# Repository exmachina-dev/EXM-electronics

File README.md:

```
____ _  _ _  _    ____ _    ____ ____ ___ ____ ____ _  _ _ ____ ____ 
|___  \/  |\/| __ |___ |    |___ |     |  |__/ |  | |\ | | |    [__  
|___ _/\_ |  |    |___ |___ |___ |___  |  |  \ |__| | \| | |___ ___] 
                                                                      
```

# EXM electronics

This repo contains all necessary files to design and produce PCBs for the ExMachina product range.

## File format and folder structure

Documentation files should be in PDF. Board image files can be in PNG or PDF.

PCB design files are in EAGLE Standard edition (7.4) file format.

The following are general rules to help maintain a consistent folder structure:

* All libraries are placed inside the shared libraries repository. It can be found
  on [Github](https://github.com/exmchina-dev/eagle-resources)

* One board for each project folder.  

* Mutiples revisions can be placed inside a subfolder. i.e. `SwitchEthernet/Rev A1`

* BOMs, partlists, spreadsheet and Gerber should placed inside a `MDP/` folder.  

## STATUS
|		Board		|	Rev  |		|
|-------------------|--------|------|
|DMX Proto			| Rev A1 | :ok: |
|Emergency Stop 	| Rev A3 | :ok: |
|EXM Encoder 		| Rev A1 | :ok: |
|EXM HMI LED 		| Rev A1 | :ok: |
|EXM Relay Four		| Rev A1 | :ok: |
|EXM Relay One		| Rev A3 | :ok: |
|EXM Relay Three	| Rev A2 | :ok: |
|Switch Ethernet 	| Rev A5 | :ok: |

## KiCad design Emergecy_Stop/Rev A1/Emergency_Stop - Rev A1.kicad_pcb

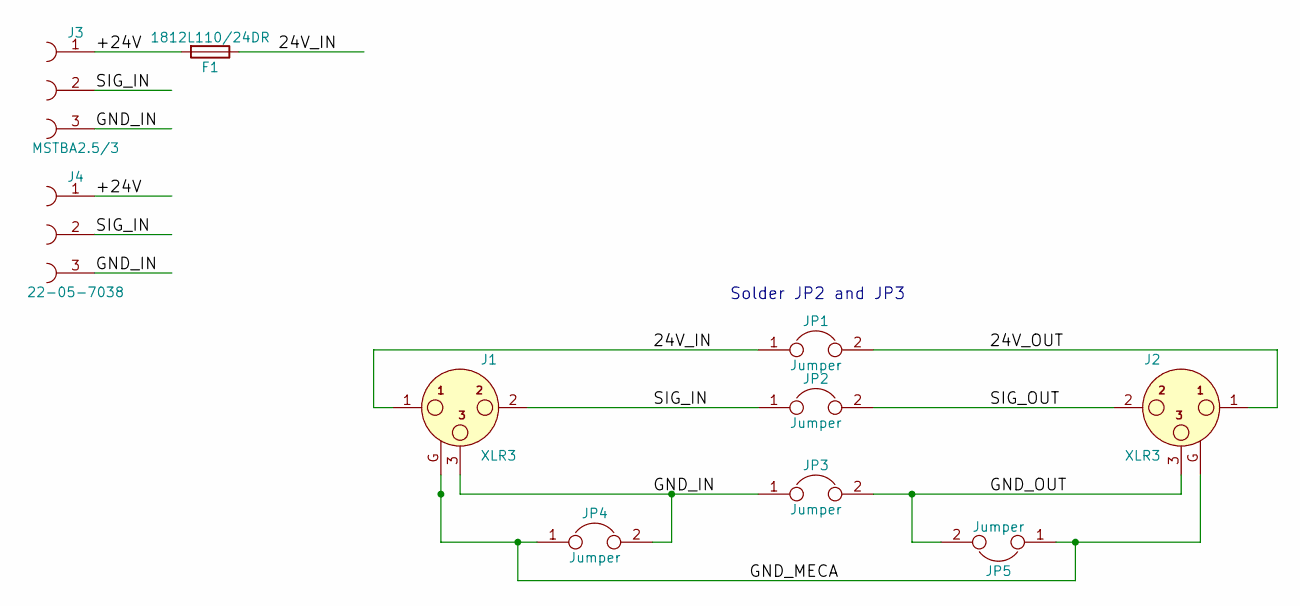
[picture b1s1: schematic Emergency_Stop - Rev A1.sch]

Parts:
F1: 1812L110/24DR; LittleFuse_1812L
J1: XLR3; NC3FAV2
J2: XLR3; NC3MAV
J3: MSTBA2.5/3; MSTBA3
J4: 22-05-7038
JP1, JP2, JP3, JP4, JP5: Jumper; GS2

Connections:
/24V_IN: F1.1, J1.1, JP1.1
/24V_OUT: J2.1, JP1.2
/+24V: F1.2, J3.1, J4.1
/GND_IN: J1.3, J3.3, J4.3, JP3.1, JP4.2
/GND_MECA: J1.G (GROUND), J2.G (GROUND), JP4.1, JP5.1
/GND_OUT: J2.3, JP3.2, JP5.2
/SIG_IN: J1.2, J3.2, J4.2, JP2.1
/SIG_OUT: J2.2, JP2.2

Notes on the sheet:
Solder JP2 and JP3

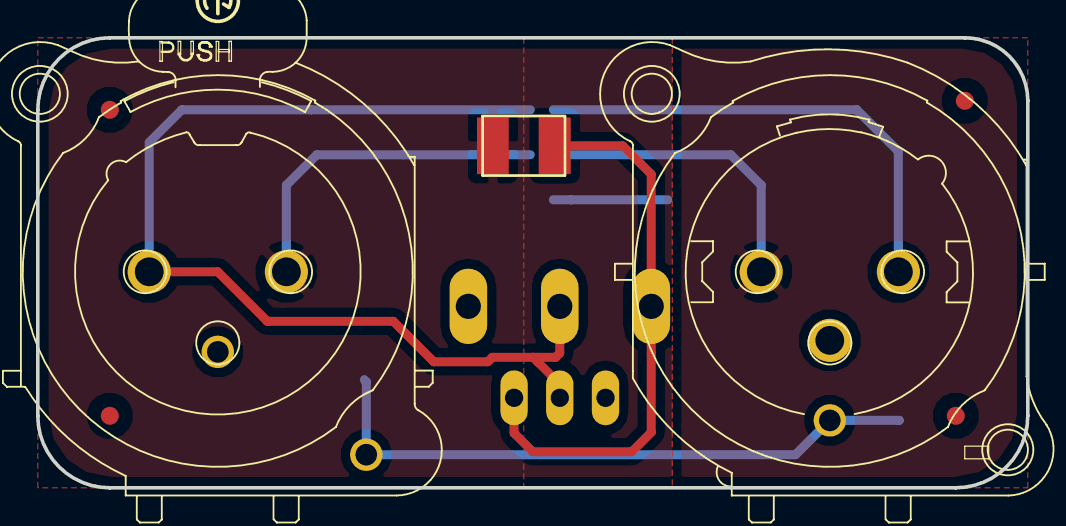
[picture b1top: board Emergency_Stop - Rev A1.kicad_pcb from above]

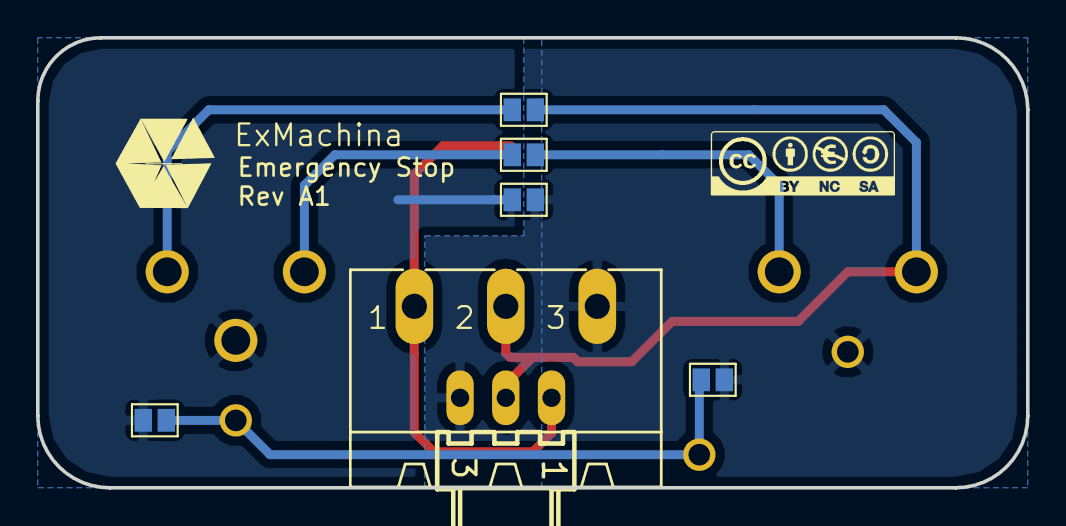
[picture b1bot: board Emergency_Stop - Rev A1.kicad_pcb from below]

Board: 2 copper layers, 55.0 x 25.0 mm, 12 parts (9 on the bottom side), 8 nets.

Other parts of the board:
S?: CC-BY-NC-SA
T3: EXMACHINA-LOGO-NAME; EXM-LOGO-BASELINE

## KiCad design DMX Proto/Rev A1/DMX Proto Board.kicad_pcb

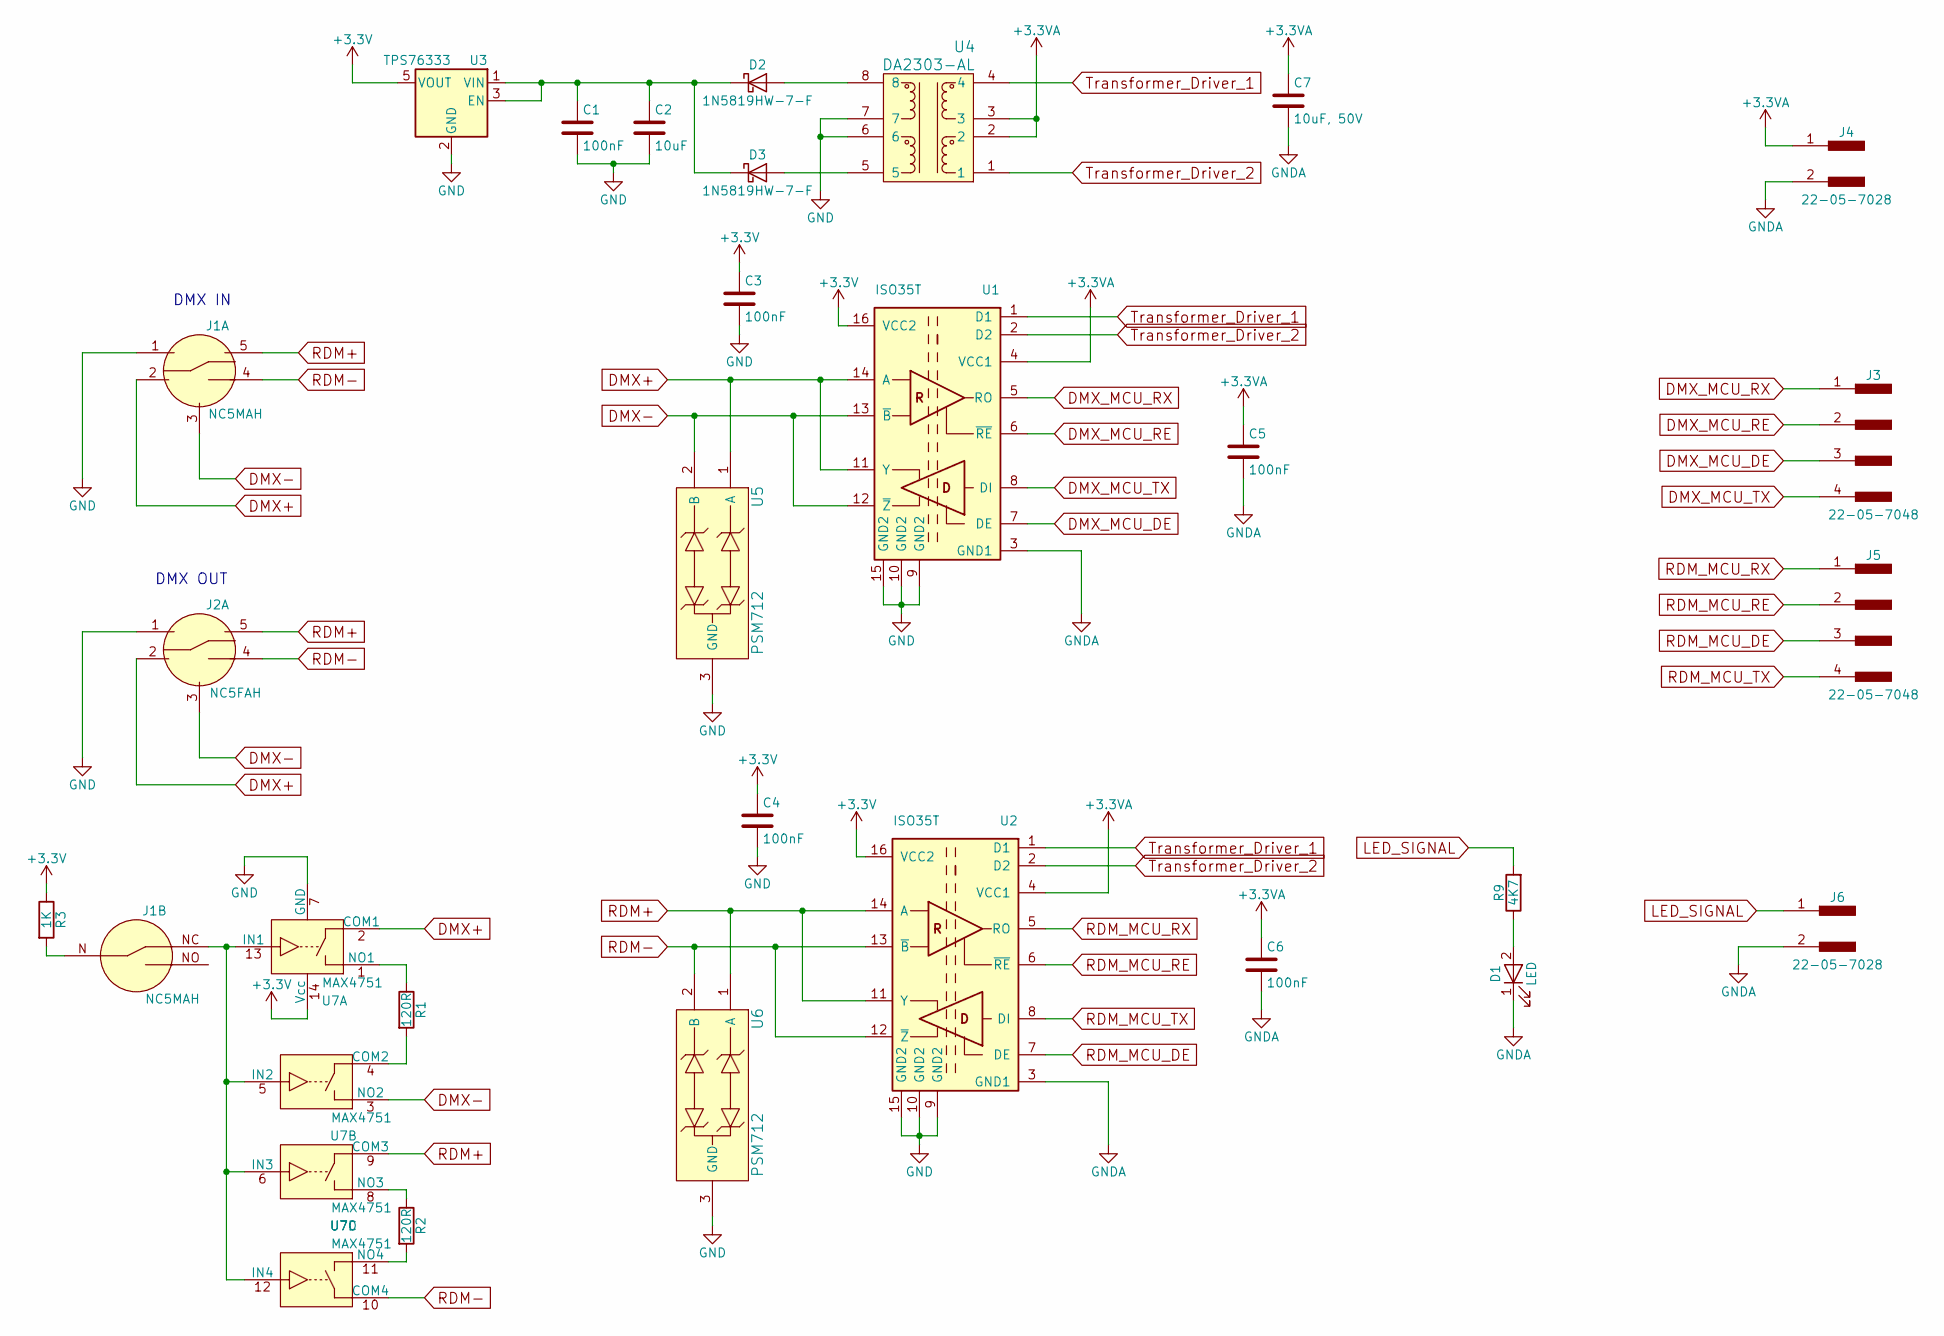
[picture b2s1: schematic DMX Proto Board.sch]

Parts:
C1, C3, C4, C5, C6: 100nF; C_0603_HandSoldering
C2: 10uF; C_0805_HandSoldering
C7: 10uF, 50V; C_0805_HandSoldering
D1: LED; LED_0603_HandSoldering
D2, D3: 1N5819HW-7-F; D_SOD-123
J1: NC5MAH; NC5MAV-SW
J2: NC5FAH; NC5FAV-SW
J3, J5: 22-05-7048; Socket_MOLEX-KK-RM2-54mm_Lock_4pin_straight
J4, J6: 22-05-7028; 7395-02
R1, R2: 120R; R_0603_HandSoldering
R3: 1K; R_0603_HandSoldering
R9: 4K7; R_0603_HandSoldering
U1, U2: ISO35T; SOIC-16_3.9x9.9mm_Pitch1.27mm
U3: TPS76333; SOT-23-5
U4: DA2303-AL; transformer-8-10x12.07
U5, U6: PSM712; SOT-23
U7: MAX4751; TSSOP-14_4.4x5mm_Pitch0.65mm

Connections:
+3.3VA: C5.1, C6.1, C7.1, J4.1, U1.4 (VCC1), U2.4 (VCC1), U4.2, U4.3
+3V3: C3.1, C4.1, R3.1, U1.16 (VCC2), U2.16 (VCC2), U3.5 (VOUT), U7.14 (Vcc)
DMX+: J1.2, J2.2, U1.11 (Y), U1.14 (A), U5.1 (A), U7.2 (COM1)
DMX-: J1.3, J2.3, U1.12 (~Z~), U1.13 (~B), U5.2 (B), U7.3 (NO2)
DMX_MCU_DE: J3.3, U1.7 (DE)
DMX_MCU_RE: J3.2, U1.6 (~RE)
DMX_MCU_RX: J3.1, U1.5 (RO)
DMX_MCU_TX: J3.4, U1.8 (DI)
GND: C1.2, C2.2, C3.2, C4.2, J1.1, J2.1, U1.9 (GND2), U1.10 (GND2), U1.15 (GND2), U2.9 (GND2), U2.10 (GND2), U2.15 (GND2), U3.2 (GND), U4.6, U4.7, U5.3 (GND), U6.3 (GND), U7.7 (GND)
GNDA: C5.2, C6.2, C7.2, D1.1 (K), J4.2, J6.2, U1.3 (GND1), U2.3 (GND1)
LED_SIGNAL: J6.1, R9.2
unnamed: C1.1, C2.1, D2.1 (K), D3.1 (K), U3.1 (VIN), U3.3 (EN)
unnamed: D1.2 (A), R9.1
unnamed: D2.2 (A), U4.8
unnamed: D3.2 (A), U4.5
unnamed: J1.N, R3.2
unnamed: J1.NC, U7.5 (IN2), U7.6 (IN3), U7.12 (IN4), U7.13 (IN1)
unnamed: R1.1, U7.1 (NO1)
unnamed: R1.2, U7.4 (COM2)
unnamed: R2.1, U7.8 (NO3)
unnamed: R2.2, U7.11 (NO4)
RDM+: J1.5, J2.5, U2.11 (Y), U2.14 (A), U6.1 (A), U7.9 (COM3)
RDM-: J1.4 (P3), J2.4 (P3), U2.12 (~Z~), U2.13 (~B), U6.2 (B), U7.10 (COM4)
RDM_MCU_DE: J5.3, U2.7 (DE)
RDM_MCU_RE: J5.2, U2.6 (~RE)
RDM_MCU_RX: J5.1, U2.5 (RO)
RDM_MCU_TX: J5.4, U2.8 (DI)
Transformer_Driver_1: U1.1 (D1), U2.1 (D1), U4.4
Transformer_Driver_2: U1.2 (D2), U2.2 (D2), U4.1

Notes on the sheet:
DMX IN
DMX OUT

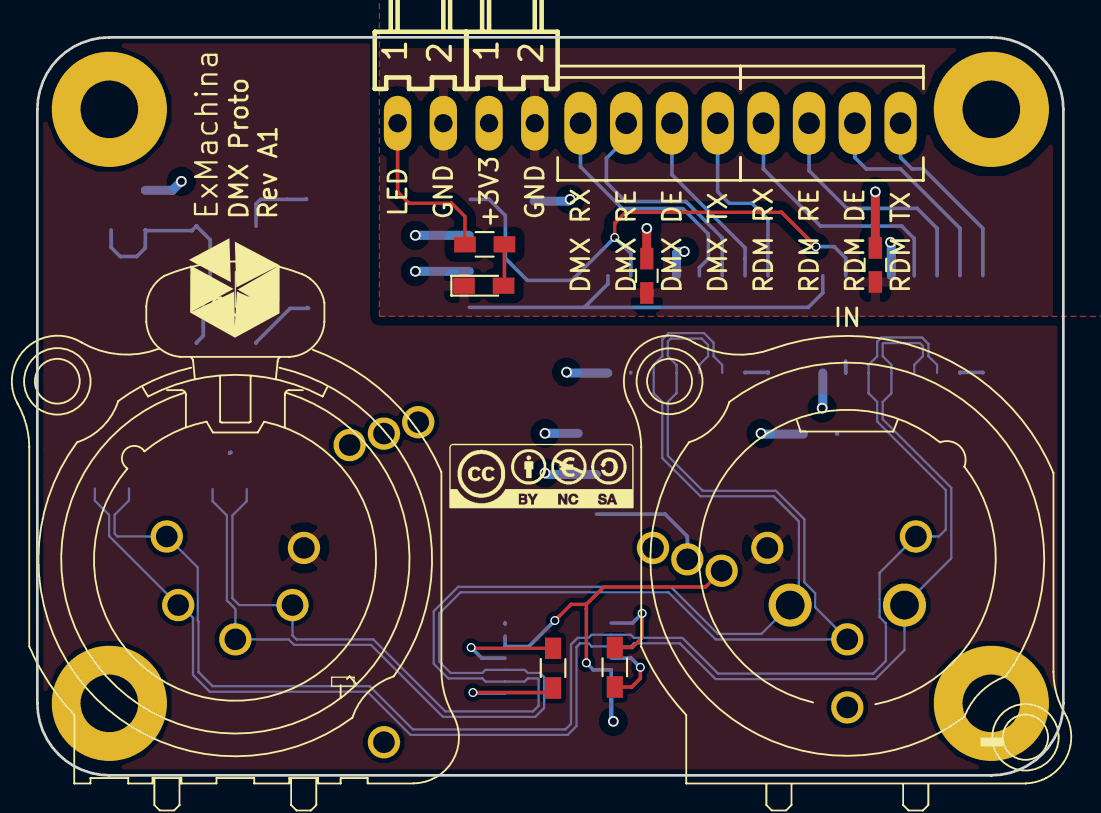
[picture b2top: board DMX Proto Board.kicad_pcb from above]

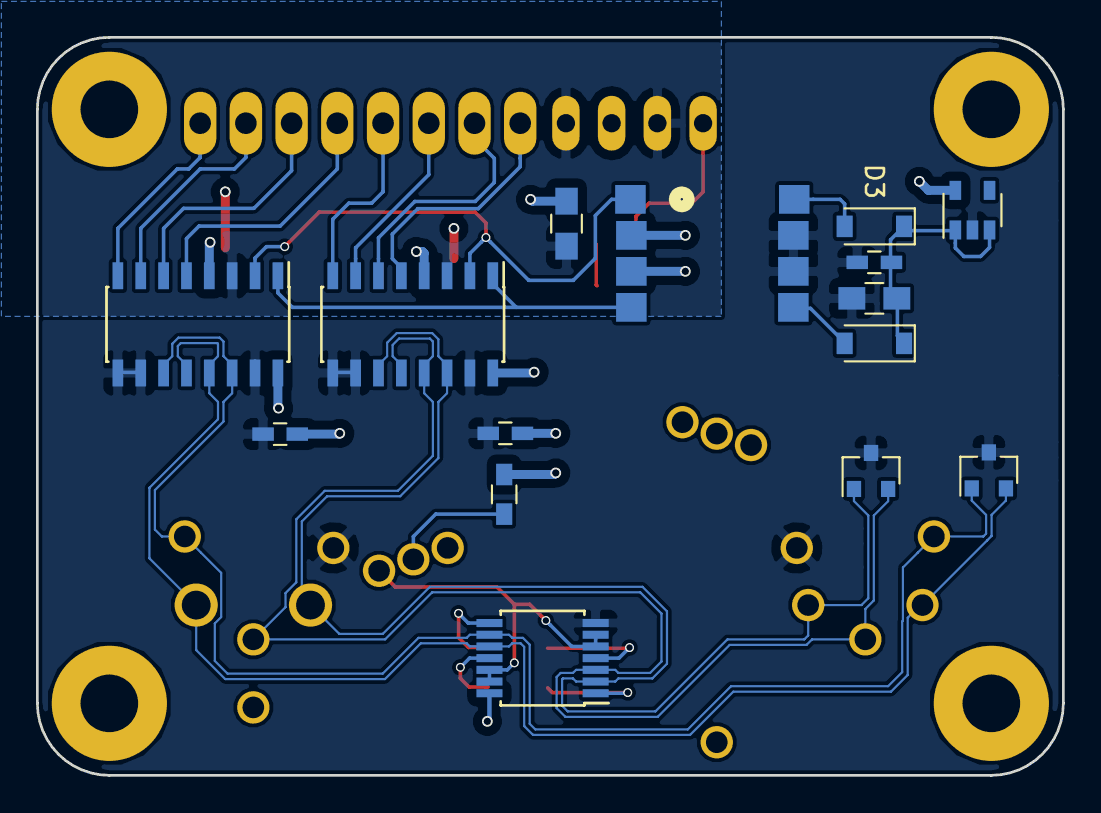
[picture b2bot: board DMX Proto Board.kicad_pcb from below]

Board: 4 copper layers, 57.0 x 41.0 mm, 29 parts (15 on the bottom side), 29 nets.

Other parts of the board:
S?: CC-BY-NC-SA
T3: EXMACHINA-LOGO-NAME; EXM-LOGO-BASELINE

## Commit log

2017-03-01 Clean repo
2017-03-01 Rename ArmazEthernet into SwitchEthernet
2017-03-01 Change description and create Switch-Ethernet Rev A3
2017-03-01 Update Description and Readme
2017-03-03 Rename .sch and .brd
2017-03-03 Preplace component on the board
2017-03-03 Connect board-to board connector
2017-03-07 Update connector and route eth 1,2 and 3
2017-03-07 Reroute ETH signals
2017-03-07 Route the spi nets
2017-03-08 Change to the top the RJ45 connector and re-route it
2017-03-08 change position of the resistors of neutrix connectors and re-route
2017-03-08 Route the board
2017-03-08 Route LED +5V
2017-03-09 Finish the routing
2017-03-13 Add bRestrict on the Neutrix panel and route GND nets
2017-04-24 Adjust connector possition and panelize the board
2017-04-25 Add via to the guard ring
2017-04-25 Connect GND meca of the connectors to the guard ring
2017-04-26 Add the cotation, the board name, the logo and the CC
2017-04-27 Adjut LED position on the board
2017-05-02 lear clearance on net and angle
2017-05-02 Replace J2 to femal connector and reroute the board, replace holes
2017-05-04 Modified the board according to the review
2017-05-04 Add operating voltage and consumption on silkscreen
2017-05-09 Rename guard ring on inner layer
2017-05-09 Update dimension layer
2017-05-09 Update silkscreen
2017-05-09 Fix keepout polygon on filters
2017-05-09 Update libraries and minor tweaks (keepouts)
2017-05-09 Fixed missing connection to GND
2017-05-09 Place name and value correctly on the board
2017-05-09 Create MDP folder and add placement top and bottom
2017-05-11 Generate MDP
2017-05-11 Replace device name on D2 and C3, C7, C19
2017-05-17 Add emergency stop board
2017-05-18 Modify power connector
2017-06-06 Finishing emergency stop board and generate MDP folder
2017-06-06 Archive gerber files and update BOM
2017-06-07 generate MDP folder
2017-06-07 Move JP4 and route the GND_MECA
2017-06-09 Generate BOM and gerber
2017-07-18 Add DMX proto board
2017-07-20 change dmx buffer
2017-07-20 Add power isolation to the schematic
2017-07-20 Add capsitor on the power
2017-07-21 Add Transint proction and name's net of the output
2017-08-03 Route the board and generate gerber
2017-10-06 Create Rev A2 of Emergency Stop board
2017-10-06 Update BOM
2017-10-06 Replace MSTBA with Molex headers and reroute
2017-10-06 Renamed dir and files (Emergency_Stop)
2017-10-09 Add MDP files
2017-10-13 Add BPtoJTAG_ICSP board files
2017-11-13 Add EmergencyStop - Rev A3 schematics and pcb design
2017-11-13 Update EmergencyStop - Rev A3
    - Fix layout
    - Major redesign in schematics
    - Add Lamp output
    - Add onboard led
2017-11-16 create EXM Relay one from eisla Armaz Relay
2017-11-16 Generate MDP files
2017-11-16 Generated Gerber files
2017-11-16 Create 3 relays board
2017-11-28 Change LED ethernet
2017-11-28 Clean repos + generated mechanical drawing
2017-11-28 Re-route the ethernet leds
2017-11-28 Update relay symbole and re-route the board
2017-11-28 Update relay device and re-route the board
2017-11-28 Rename .sch and .brd to relay three
2017-11-28 Clean the folder and repair .sch file
2017-11-28 Create EXM Relay four board
2017-12-06 Renumber outputs and change silkscreen
2017-12-06 Generate Gerber
2017-12-15 Create EXM HMI LED Rev A1 board
2017-12-15 Generated gerber
2017-12-15 Generated BOM files
2017-12-15 Create EXM Relay Three Rev A2, add C on each relay interface
2017-12-15 Renumber part and updated BOM
2017-12-15 Create EXM Encoder project
2017-12-15 Generated MDP files
2017-12-15 Finish to route the board
2017-12-18 Reorganization of schematic layouts
2017-12-18 Fix bad revision name on CPU board
2017-12-18 Don't mirror the layer identifier 2
2017-12-18 Update schematic and board due to the update of encoder symbol
2017-12-18 Add bottom silkscreen on EXM Encoder
2017-12-18 Update from libraries:
    - `con-molex`
    - `encoder.lbr`
2017-12-20 Create EXM Safety Stop board
2017-12-20 Generated Gerber of EXM HMI LED Rev A1
2017-12-21 Final revision before review:
    - Update package silkscreen
    - Reroute to prevent GND from being broke
    - Change signal trace width to 8mil
    - Change power trace width to 12mil
    - Connect FTDI +5V to converter instead of VDD
2017-12-22 Add LED dimensions
2017-12-22 Final modifications before MDP in EXM Safety board - Rev A1:
    - Renamed signal +24V_IN to +24V_PS
    - Named signal +24V_IN
    - Connect +24V_OUT after the fuse
2017-12-22 Change width for LED trace
2017-12-22 Update EXM - Safety Board - Rev A1 form libraries
2017-12-22 Renamed EXM Safety Stop to EXM Safety Board
2018-01-03 Generated MDP files of EXM Encoder Rev A1
2018-01-03 Switch Ethernet Rev A6 : Deplace some via and replace the fuse
2018-01-31 Generate MDP for BPtoJTAG_ISCP
2018-01-31 Add EXM Relay One rev A3
2018-01-31 generated MDP files of Ethernet switch rev A6
